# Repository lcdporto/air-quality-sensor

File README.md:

# air-quality-sensor
A Home Assistant compatible device

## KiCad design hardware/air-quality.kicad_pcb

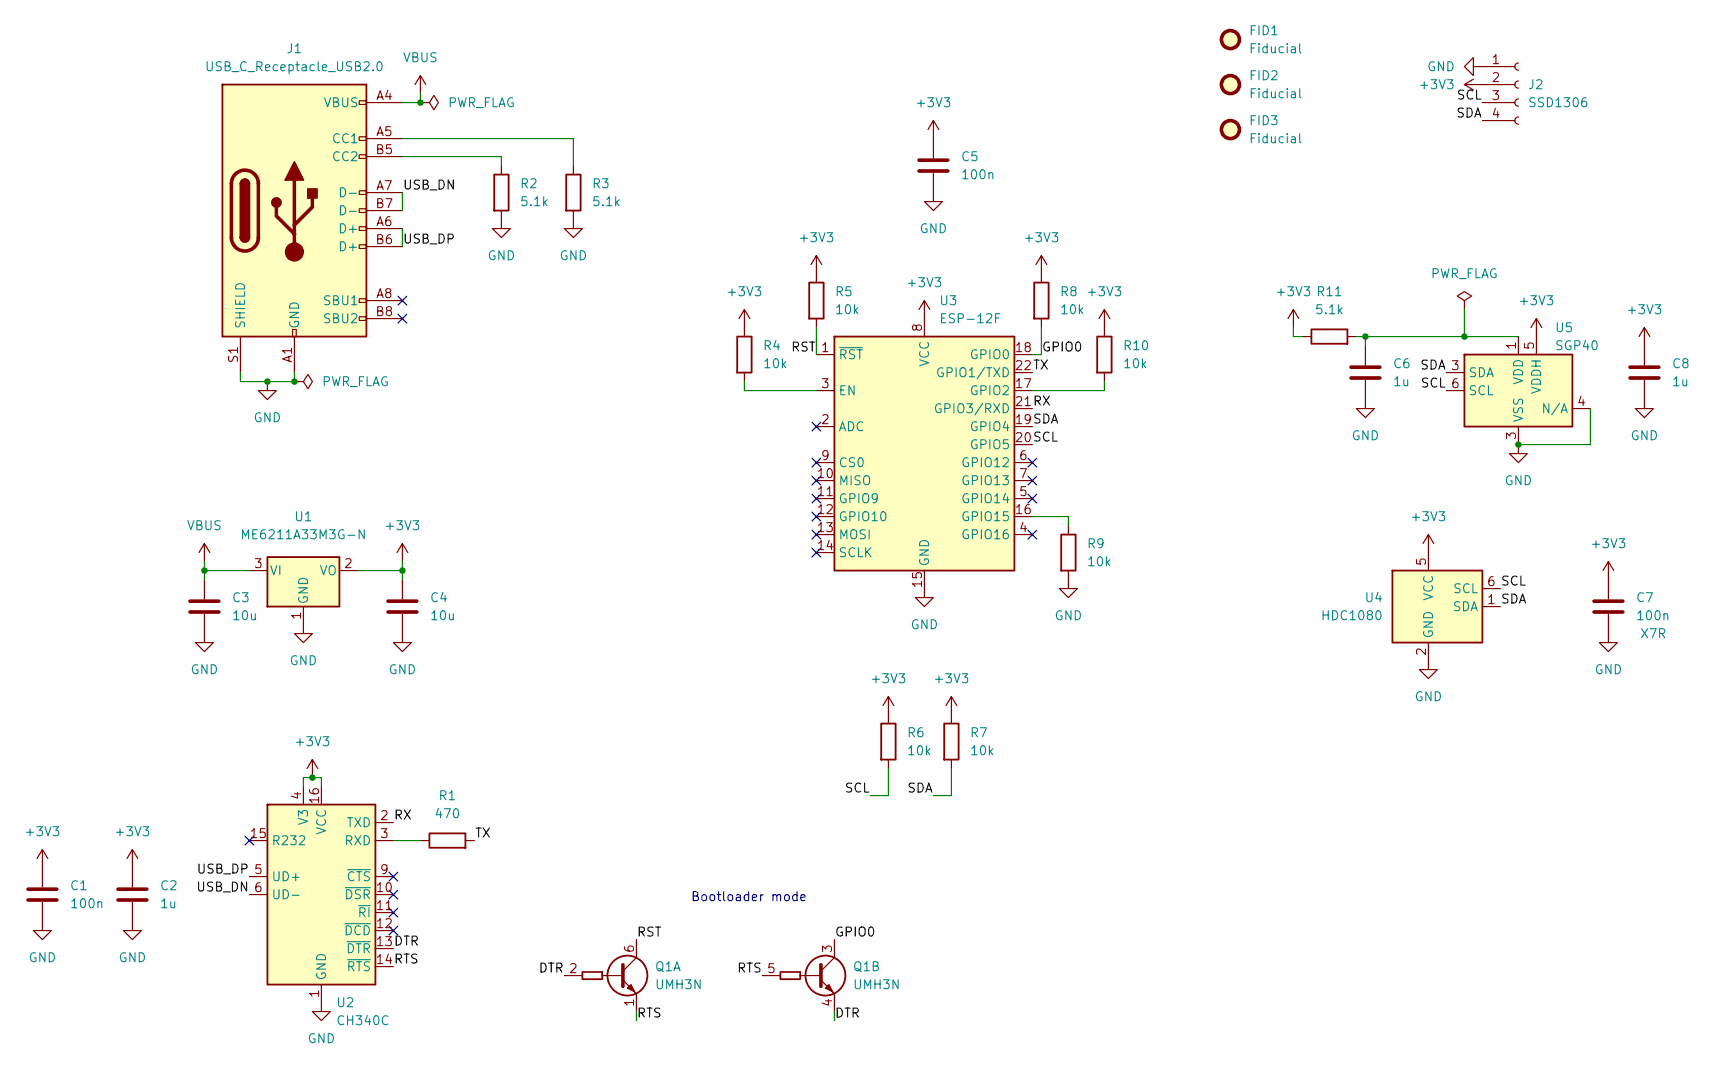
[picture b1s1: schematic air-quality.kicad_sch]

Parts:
C1, C5, C7: 100n; C_0805_2012Metric; LCSC C476766
C2, C6, C8: 1u; C_0805_2012Metric; LCSC C16834
C3, C4: 10u; C_0805_2012Metric; LCSC C17024
FID1, FID2, FID3: Fiducial; Fiducial_0.5mm_Mask1mm
J1: USB_C_Receptacle_USB2.0; USB_C_Receptacle_Palconn_UTC16-G; LCSC C165948
J2: SSD1306; PinSocket_1x04_P2.54mm_Vertical
Q1: UMH3N; SOT-363_SC-70-6; LCSC C62892
R1: 470; R_0805_2012Metric; LCSC C119076
R2, R3, R11: 5.1k; R_0805_2012Metric; LCSC C115337
R4, R5, R6, R7, R8, R9, R10: 10k; R_0805_2012Metric; LCSC C115295
U1: ME6211A33M3G-N; SOT-23; LCSC C168807
U2: CH340C; SOIC-16_3.9x9.9mm_P1.27mm; LCSC C84681
U3: ESP-12F; ESP-12E; LCSC C82891
U4: HDC1080; Texas_PWSON-N6; LCSC C82227
U5: SGP40; DFN-6-1EP_2.44x2.44mm_P0.8mm_EP1.25x1.64mm

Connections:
+3V3: C1.1, C2.1, C4.1, C5.1, C7.1, C8.1, J2.2, R4.1, R5.1, R6.1, R7.1, R8.1, R10.1, R11.1, U1.2 (VO), U2.4 (V3), U2.16 (VCC), U3.8 (VCC), U4.5 (VCC), U5.5 (VDDH)
/DTR: Q1.2 (B1), Q1.4 (E2), U2.13 (~DTR)
/GPIO0: Q1.3 (C2), R8.2, U3.18 (GPIO0)
/RST: Q1.6 (C1), R5.2, U3.1 (~RST)
/RTS: Q1.1 (E1), Q1.5 (B2), U2.14 (~RTS)
/RX: U2.2 (TXD), U3.21 (GPIO3/RXD)
/SCL: J2.3, R6.2, U3.20 (GPIO5), U4.6 (SCL), U5.6 (SCL)
/TX: R1.2, U3.22 (GPIO1/TXD)
/USB_DN: J1.A7 (D-), J1.B7 (D-), U2.6 (UD-)
/USB_DP: J1.A6 (D+), J1.B6 (D+), U2.5 (UD+)
unnamed: C6.1, R11.2, U5.1 (VDD)
unnamed: J1.A5 (CC1), R3.1
unnamed: J1.B5 (CC2), R2.1
unnamed: R1.1, U2.3 (RXD)
unnamed: R4.2, U3.3 (EN)
unnamed: R9.1, U3.16 (GPIO15)
unnamed: R10.2, U3.17 (GPIO2)
VBUS: C3.1, J1.A4 (VBUS), J1.A9 (VBUS), J1.B4 (VBUS), J1.B9 (VBUS), U1.3 (VI)

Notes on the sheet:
Bootloader mode

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
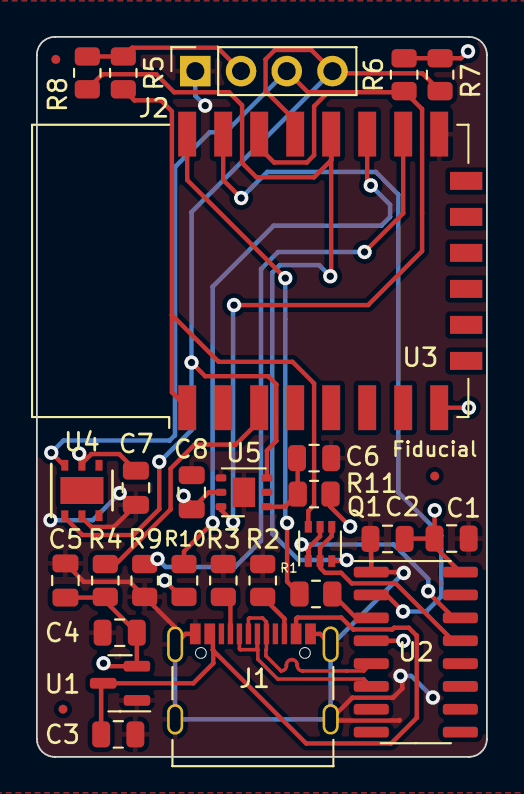
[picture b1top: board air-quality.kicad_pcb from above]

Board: 2 copper layers, 25.0 x 40.0 mm, 30 parts (0 on the bottom side), 20 nets.

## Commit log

2022-01-04 PCB design
2022-01-20 Added display
2022-01-20 Configure gerbers
2022-01-22 Add automatic artifact generation
2022-01-22 Fix some names on script
2024-11-22 Update to KiCAD v8
2025-02-07 Atualizar o generate-pcb-artifacts.yaml
2025-02-07 Update project
2025-03-12 Added ESPHome configuration
